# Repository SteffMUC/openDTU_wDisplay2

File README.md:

# openDTU_wDisplay2 

* Small PCB for [openDTU](https://github.com/tbnobody/OpenDTU)
* Based on idea/ realization of [breakout board](https://github.com/dokuhn/openDTU-BreakoutBoard)
* 2nd version with much smaller PCB [1st version](https://github.com/SteffMUC/openDTU_wDisplay)
* The PCB has the ESP32 on backside, Display and nRF24l01 on frontside.
* Dedicated case available in [openscad](https://github.com/SteffMUC/openDTU_wDisplay2/tree/main/openscad) directory
* Configuration file [nodemcu_esp32.json](https://github.com/tbnobody/OpenDTU/blob/master/docs/DeviceProfiles/nodemcu_esp32.json) available in [openDTU](https://github.com/tbnobody/OpenDTU), please select "Generic NodeMCU 32 with SSD1306" as profile
* In case you struggle how to configure [openDTU](https://github.com/tbnobody/OpenDTU), the documentation can be found here [openDTU Display documentation](https://github.com/tbnobody/OpenDTU/blob/master/docs/Display.md)
* The PCB is designed to work with ESP32S NodeMCU (38 Pins) e.g. [Amazon](https://www.amazon.de/gp/product/B0BF5NRF8H/ref=ppx_yo_dt_b_search_asin_title?ie=UTF8&th=1)

## Picture of model:

## Final printed case with display mounted on the side of a small IKEA Besta cupboard:

## PCB assembly:

## History:

* 2023-02-28: boards received, soldered, working reliable, pics in picture folder, case currently in progress - not yet perfectly fitting 

* 2023-03-01: Final printing of case done, got some requests for spare PCBs, all spare PCBs now gone, if you need a PCB, you can easily upload the gerber zip file on any PCB manufacturer, e.g. PLCPCB (10 pieces, with customs to Germany in 2 weeks roughly 14 EUR).

* 2023-03-11: Accepted pull request from @Nightreaver, thanks for the contribution, backside silk screen now mirrored, nRF footprint changed by @Nightreaver to support nRF+ with antenna (Note: openscad case not adapted and currently not planned to be adapted)

In case you are looking for a cheap source for the capacitors, I ordered mine with Christians_Shop at [Amazon](https://www.amazon.de/gp/product/B01MTSDA58/ref=ppx_yo_dt_b_search_asin_title?ie=UTF8&psc=1) (they have a direct website as well).

## 3D Print:
Everything can be printed without support, expect for the ikea holder:

## Known limitations: 
* Backside silkscreen is not mirrored, in Kicad, still needs to be fixed, result is mirrored text on backside (for new orders). --> Fixed now
* If you print the case: The holders for the PCB are not yet perfectly aligned (need 0.5mm adjust), I "clipped" 3 of them away to avoid reprinting.

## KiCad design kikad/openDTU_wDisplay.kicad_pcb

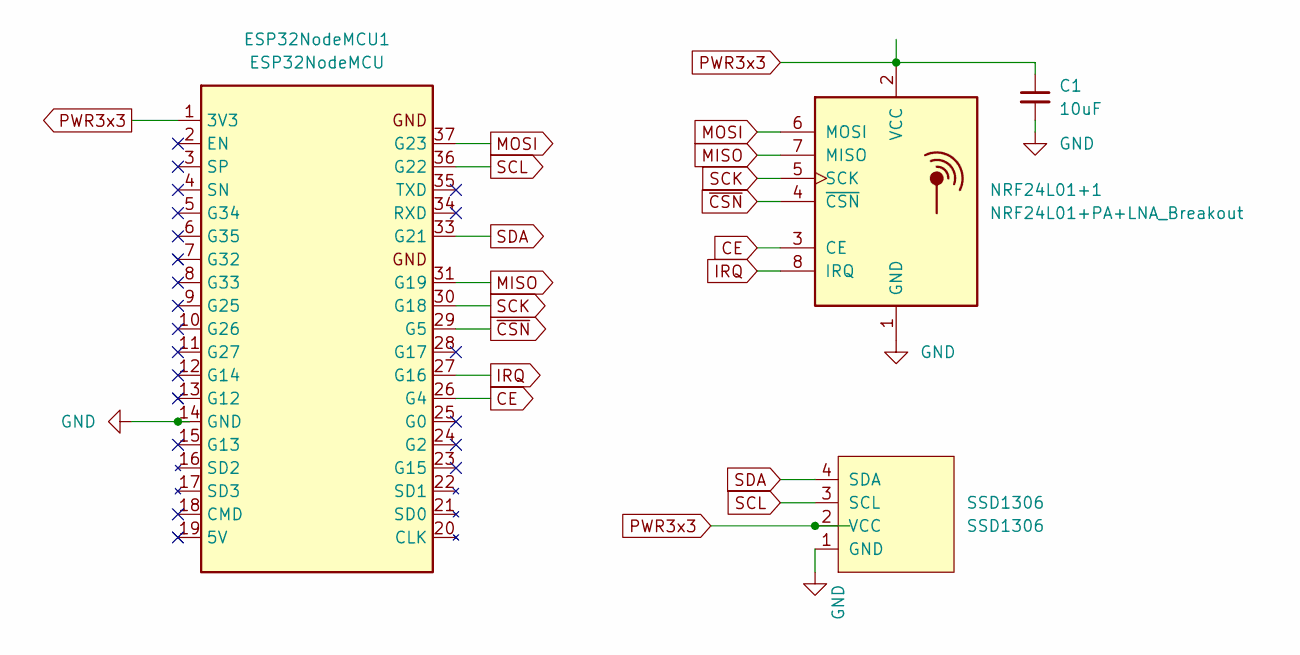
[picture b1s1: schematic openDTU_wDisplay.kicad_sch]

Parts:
C1: 10uF; C_Radial_D4.0mm_H5.0mm_P1.50mm
ESP32NodeMCU1: ESP32NodeMCU; ESP32-NodeMCU_WROOM_32
NRF24L01+1: NRF24L01+PA+LNA_Breakout; nRF24L01+PA+LNA_Breakout
SSD1306: SSD1306; 128x64OLED

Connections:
CE: ESP32NodeMCU1.26 (G4), NRF24L01+1.3 (CE)
GND: C1.2, ESP32NodeMCU1.14 (GND), ESP32NodeMCU1.32 (GND), ESP32NodeMCU1.38 (GND), NRF24L01+1.1 (GND), SSD1306.1 (GND)
IRQ: ESP32NodeMCU1.27 (G16), NRF24L01+1.8 (IRQ)
MISO: ESP32NodeMCU1.31 (G19), NRF24L01+1.7 (MISO)
MOSI: ESP32NodeMCU1.37 (G23), NRF24L01+1.6 (MOSI)
PWR3x3: C1.1, ESP32NodeMCU1.1 (3V3), NRF24L01+1.2 (VCC), SSD1306.2 (VCC)
SCK: ESP32NodeMCU1.30 (G18), NRF24L01+1.5 (SCK)
SCL: ESP32NodeMCU1.36 (G22), SSD1306.3 (SCL)
SDA: ESP32NodeMCU1.33 (G21), SSD1306.4 (SDA)
~CSN: ESP32NodeMCU1.29 (G5), NRF24L01+1.4 (~CSN)

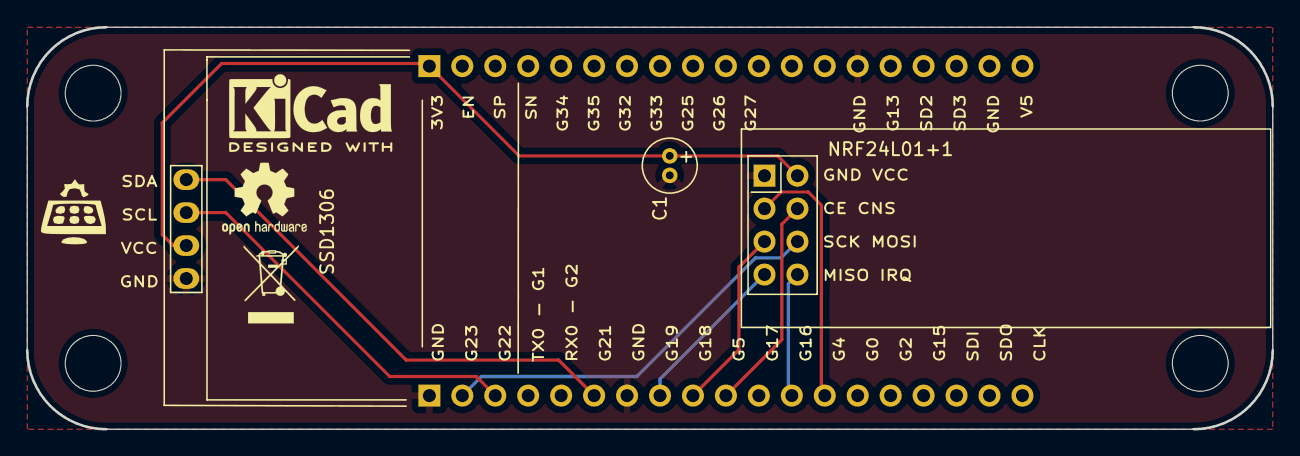
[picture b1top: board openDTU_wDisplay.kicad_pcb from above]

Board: 2 copper layers, 96.0 x 31.0 mm, 4 parts (1 on the bottom side), 10 nets.

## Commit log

2023-02-16 Create LICENSE
2023-02-16 3dboard
2023-02-16 stl plus wrl model exported
2023-02-17 v2 case 1st draft
2023-02-25 holder + spacer
2023-02-27 new pics
2023-02-27 adaption of display location
2023-02-28 case corrections
2023-02-28 adapt ikea holder
2023-03-01 change angle for ikea holder
2023-03-03 pics of holder
2023-03-10 add support for NRF with external antenna shrink photos

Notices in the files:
README.md:
License: CC BY-NC-SA 4.0
